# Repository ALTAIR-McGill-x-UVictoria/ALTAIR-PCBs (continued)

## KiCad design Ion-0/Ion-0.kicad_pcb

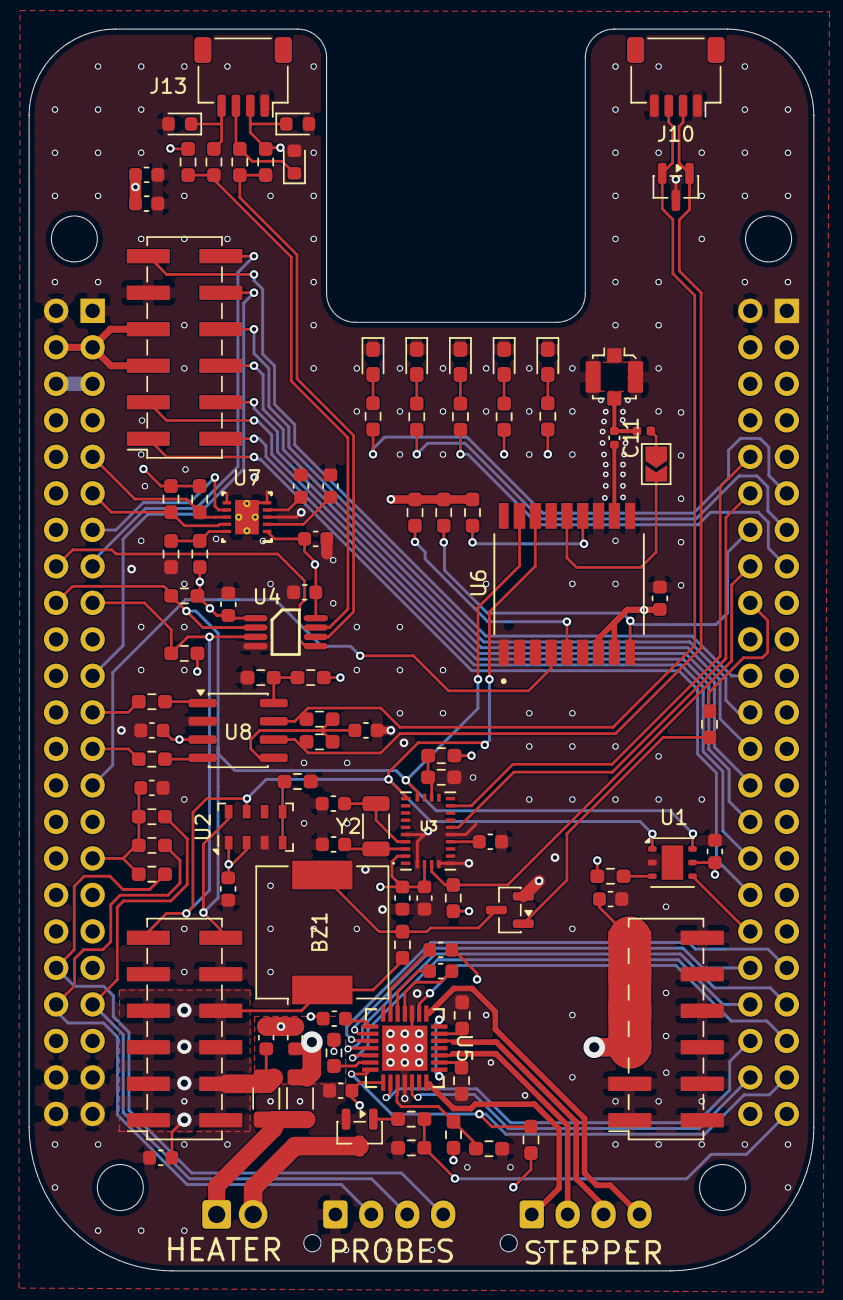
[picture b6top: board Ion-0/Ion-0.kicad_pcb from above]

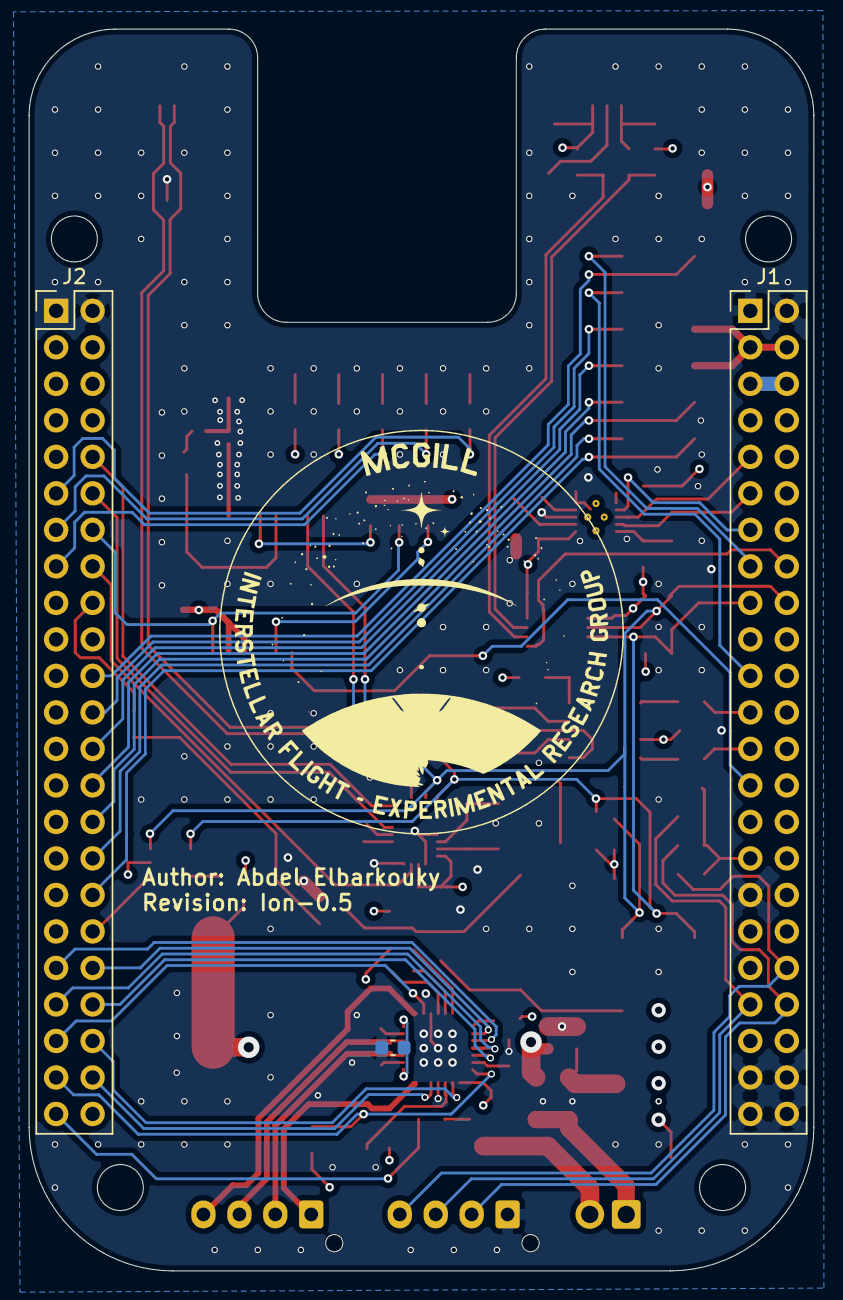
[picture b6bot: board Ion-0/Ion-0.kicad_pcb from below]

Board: 4 copper layers, 54.6 x 86.4 mm, 106 parts (3 on the bottom side), 91 nets.

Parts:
BZ1: Buzzer; Buzzer_CUI_CPT-9019S-SMT
C1, C7, C10, C12, C13, C15, C18, C19, C20, C22, C25, C26: 100nF; C_0603_1608Metric
C2, C3: 22pF; C_0603_1608Metric
C4, C5, C6: 0.1uF; C_0603_1608Metric
C8, C23: 1uF; C_0603_1608Metric
C9: 100pF; C_0603_1608Metric
C11: 47pF; C_0402_1005Metric
C14, C16, C17: 22uF; C_0603_1608Metric
C21: 4.7nF; C_0603_1608Metric
C27, C28: 0.22uF; C_0603_1608Metric
C29: 100uF; C_0603_1608Metric
D1: ESD3V3T2BHE3; SOT-23
D2, D3, D4, D5, D6: LED; LED_0603_1608Metric_Pad1.05x0.95mm_HandSolder
D7, D8, D9: TVS_3V3; D_0603_1608Metric
J1: Beaglebone-green-P9; PinHeader_2x23_P2.54mm_Vertical
J2: Beaglebone-green-P8; PinHeader_2x23_P2.54mm_Vertical
J3, J4, J5: Conn_02x06_Odd_Even; PinSocket_2x06_P2.54mm_Vertical_SMD
J6: Coaxial_Small; U.FL_Molex_MCRF_73412-0110_Vertical
J7: Conn_Probs; JST_XH_B4B-XH-AM_1x04_P2.50mm_Vertical
J8: Conn_Heater; TerminalBlock_Xinya_XY308-2.54-2P_1x02_P2.54mm_Horizontal
J10: Conn_CAN; JST_SH_SM04B-SRSS-TB_1x04-1MP_P1.00mm_Horizontal
J13: Conn_01x04; JST_SH_SM04B-SRSS-TB_1x04-1MP_P1.00mm_Horizontal
J15: Conn_01x04; JST_XH_B4B-XH-AM_1x04_P2.50mm_Vertical
JP5: SolderJumper_2_Open; SolderJumper-2_P1.3mm_Open_TrianglePad1.0x1.5mm
L1: 101nH; L_0402_1005Metric
Q1, Q2: IRLML6244; SOT-23
R4, R5, R41: 100K; R_0603_1608Metric_Pad0.98x0.95mm_HandSolder
R6, R7, R18: 4.7K; R_0603_1608Metric_Pad0.98x0.95mm_HandSolder
R8, R11, R14, R15, R16, R17, R22, R35, R36: 10K; R_0603_1608Metric_Pad0.98x0.95mm_HandSolder
R9, R25: DNI; R_0603_1608Metric_Pad0.98x0.95mm_HandSolder
R10, R24, R42, R47: 0; R_0603_1608Metric_Pad0.98x0.95mm_HandSolder
R12: 523; R_0603_1608Metric_Pad0.98x0.95mm_HandSolder
R13: 80.6; R_0603_1608Metric_Pad0.98x0.95mm_HandSolder
R19: 5K; R_0603_1608Metric_Pad0.98x0.95mm_HandSolder
R20: 20K; R_0603_1608Metric_Pad0.98x0.95mm_HandSolder
R21: 33K; R_0603_1608Metric_Pad0.98x0.95mm_HandSolder
R23, R28: 60; R_0603_1608Metric_Pad0.98x0.95mm_HandSolder
R26, R27: 33; R_0603_1608Metric_Pad0.98x0.95mm_HandSolder
R29: 100; R_0603_1608Metric_Pad0.98x0.95mm_HandSolder
R30: 470; R_0603_1608Metric_Pad0.98x0.95mm_HandSolder
R31: 1k; R_0603_1608Metric_Pad0.98x0.95mm_HandSolder
R32, R33, R34, R37, R38, R45, R46: 330; R_0603_1608Metric_Pad0.98x0.95mm_HandSolder
R39, R40: 0; R_1206_3216Metric
R43, R44: 0.05; R_0603_1608Metric_Pad0.98x0.95mm_HandSolder
U1: HDC2080; Texas_S-PWSON-N6-HDC2080
U2: MS5607-02BA; LGA-8_3x5mm_P1.25mm
U3: BNO085; IC_BNO085
U4: TCA9617ADGKR; TCA9617A
U5: A4988SETTR-T; QFN-28_ALM
U6: MAX-M10M-00B; XCVR_MAX-M10M-00B
U7: TPS3850H50DRCR; TPS3850
U8: SN65HVD230; SOIC-8_3.9x4.9mm_P1.27mm
Y2: 9HT10-32.768KBZF-T; L_1206_3216Metric

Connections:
+1V8: C23.2, J1.31, R4.1, R5.1, R41.1
+3V3: C1.1, C4.1, C5.1, C7.1, C10.2, C12.2, C15.1, C16.1, C19.2, C20.1, C22.2, C27.1, C28.1, D8.1 (A1), J1.3, J1.4, J5.5, J5.7, J13.2, R6.2, R7.1, R8.1, R9.1, R12.1, R14.1, R15.1, R16.2, R17.1, R18.2, R19.2, R21.1, R25.1, R30.1, R35.1, R36.1, R47.1, U1.5 (VDD), U2.1 (VDD), U2.2 (PS), U3.3 (VDD), U3.28 (VDDIO), U4.1 (VCCA), U4.8 (VCCB), U5.15 (VDD), U6.7 (V_IO), U6.8 (VCC), U7.1 (VDD), U8.3 (VCC)
+5V: BZ1.1 (+), C17.1, C18.1, J1.5, J1.6, J4.1, J4.2, J4.3, J4.4, J4.5, J4.6, J4.7, J4.8, R31.1, R39.1, R45.1
+12V: C13.1, C14.1, C26.1, C29.1, J3.5, J3.7, J3.9, J3.11, R40.1, U5.22 (VBB1), U5.28 (VBB2)
/AIN0: J1.40, J7.2, R5.2
/AIN1: J1.39, J7.3, R4.2
/AIN2: J1.38, J7.4, R41.2
/Buzzer: J2.18, R46.1
/CAN_RXD: J1.25, R27.1
/CAN_TXD: J1.23, R26.1
/GPS-PPS: J1.27, U6.4 (TIMEPULSE)
/Humidity-INT: J2.36, U1.4 (DRDY)
/I2C1B-EN: J1.16, U4.5 (EN)
/I2C1_SCL: J1.18, J4.12, R7.2, U1.6 (SCL), U2.8 (SCLK), U3.19 (H_SCL/SCK/RX), U4.2 (SCLA), U6.17 (SCL)
/I2C1_SDA: J1.17, J4.11, R6.1, U1.1 (SDA), U2.7 (SDI/SDA), U3.20 (H_SDA/H_MISO/TX), U4.3 (SDAA), U6.16 (SDA)
/IND-1: J2.13, R33.1
/IND-2: J2.11, R34.1
/IND_3: J2.22, J5.11
/LED_PWM_1: J1.21, J5.10
/LED_PWM_2: J1.15, J5.12
/MOTOR_1_A: J2.28, J5.4
/MOTOR_1_B: J2.32, J5.2
/MOTOR_2_A: J2.24, J5.8
/MOTOR_2_B: J2.26, J5.6
/PWM-Heaters: J2.45, R11.1, R29.1
/SERVO_1: J2.30, J5.3
/SERVO_2: J2.34, J5.1
/STATE-LED: J2.15, R32.1
/STP-DIR: J2.44, U5.19 (DIR)
/STP-MS1: J2.38, U5.9 (MS1)
/STP-MS2: J2.37, U5.10 (MS2)
/STP-MS3: J2.39, U5.11 (MS3)
/STP-STEP: J2.42, U5.16 (STEP)
/Sensor-bus-hat/CAN_N: D1.1 (A1), J10.2, R23.2, U8.6 (CANL)
/Sensor-bus-hat/CAN_P: D1.2 (A2), J10.3, R28.1, U8.7 (CANH)
/Sensor-bus-hat/CAN_Vref: C21.1, R23.1, R28.2, U8.5 (Vref)
/Sensor-bus-hat/OUT1A: J15.2, U5.24 (OUT1A)
/Sensor-bus-hat/OUT1B: J15.1, U5.21 (OUT1B)
/Sensor-bus-hat/OUT2A: J15.3, U5.26 (OUT2A)
/Sensor-bus-hat/OUT2B: J15.4, U5.1 (OUT2B)
/Sensor-bus-hat/VCC_RF: JP5.2 (B), U6.14 (VCC_RF)
/WD-INT: J1.13, U7.7 (WDI)
/~BNO-BOOT: J2.16, R8.2, U3.4 (~BOOT)
/~BNO-INT: J2.10, U3.14 (~H_INT)
/~BNO-RST: J2.12, U3.11 (~RST)
/~GPS-RST: J2.14, R17.2, U6.9 (~RESET)
/~STP-EN: J2.41, U5.2 (*ENABLE)
/~STP-RST: J2.40, U5.12 (*RESET)
/~STP-SLP: J2.43, R19.1, U5.14 (*SLEEP)
/~SYS_RST: J1.9, R15.2, U7.8 (WDO_N)
/~WD-RST: J1.11, R14.2, U7.9 (RESET_N)
GND: C1.2, C2.2, C3.2, C4.2, C5.2, C6.2, C7.2, C8.1, C9.2, C10.1, C12.1, C13.2, C14.2, C15.2, C16.2, C17.2, C18.2, C19.1, C20.2, C21.2, C22.1, C23.1, C27.2, C29.2, D1.3 (common), D2.1 (K), D3.1 (K), D4.1 (K), D5.1 (K), D6.1 (K), D7.2 (A2), D8.2 (A2), D9.2 (A2), J1.1, J1.2, J1.33, J1.43, J1.44, J1.45, J1.46, J2.1, J2.2, J3.1, J3.2, J3.3, J3.4, J3.6, J3.8, J3.10, J3.12, J4.9, J4.10, J5.9, J6.2 (Ext), J7.1, J10.1, J10.4, J13.1, Q1.2 (S), Q2.2 (S), R10.2, R11.2, R13.1, R20.1, R22.2, R24.2, R42.2, R43.2, R44.2, U1.2 (GND), U2.3 (GND), U3.2 (GND), U3.5 (PS1), U3.6 (PS0/WAKE), U3.10 (CLKSEL0), U3.25 (GNDIO), U4.4 (GND), U5.3 (GND), U5.18 (GND), U5.29, U6.1 (GND), U6.10 (GND__1), U6.12 (GND__2), U7.3 (SET0), U7.5 (GND), U7.6 (SET1), U7.11 (PAD), U8.2 (GND)
unnamed: BZ1.2 (-), Q1.3 (D), R45.2
unnamed: D2.2 (A), R30.2
unnamed: D3.2 (A), R31.2
unnamed: D4.2 (A), R32.2
unnamed: D5.2 (A), R33.2
unnamed: D6.2 (A), R34.2
unnamed: D7.1 (A1), J13.3, R38.2
unnamed: D9.1 (A1), J13.4, R37.2
unnamed: C11.1, J6.1 (In), L1.2
unnamed: J8.1, R39.2, R40.2
unnamed: J8.2, Q2.3 (D)
unnamed: JP5.1 (A), L1.1
unnamed: Q1.1 (G), R46.2
unnamed: Q2.1 (G), R29.2
unnamed: R42.1, U2.4 (CSB), U2.5 (CSB)
unnamed: R47.2, U1.3 (ADDR)
unnamed: C6.1, U3.9 (CAP)
unnamed: R9.2, R10.1, U3.17 (SA0/H_MOSI)
unnamed: C2.1, U3.27 (XIN32), Y2.1
unnamed: C3.1, U3.26 (XOUT32/CLKSEL1), Y2.2
unnamed: R36.2, R37.1, U4.7 (SCLB)
unnamed: R35.2, R38.1, U4.6 (SDAB)
unnamed: C25.1, U5.4 (CP1)
unnamed: C25.2, U5.5 (CP2)
unnamed: R21.2, R22.1, U5.17 (REF)
unnamed: R20.2, U5.13 (ROSC)
unnamed: R44.1, U5.23 (SENSE1)
unnamed: R43.1, U5.27 (SENSE2)
unnamed: C26.2, U5.6 (VCP)
unnamed: C28.2, U5.8 (VREG)
unnamed: R18.1, U6.5 (EXTINT)
unnamed: R16.1, U6.13 (LNA_EN)
unnamed: C11.2, U6.11 (RF_IN)
unnamed: C8.2, U7.4 (CRST)
unnamed: C9.1, U7.2 (CWD)
unnamed: R12.2, R13.2, U7.10 (SENSE)
unnamed: R26.2, U8.1 (D)
unnamed: R27.2, U8.4 (R)
unnamed: R24.1, R25.2, U8.8 (Rs)

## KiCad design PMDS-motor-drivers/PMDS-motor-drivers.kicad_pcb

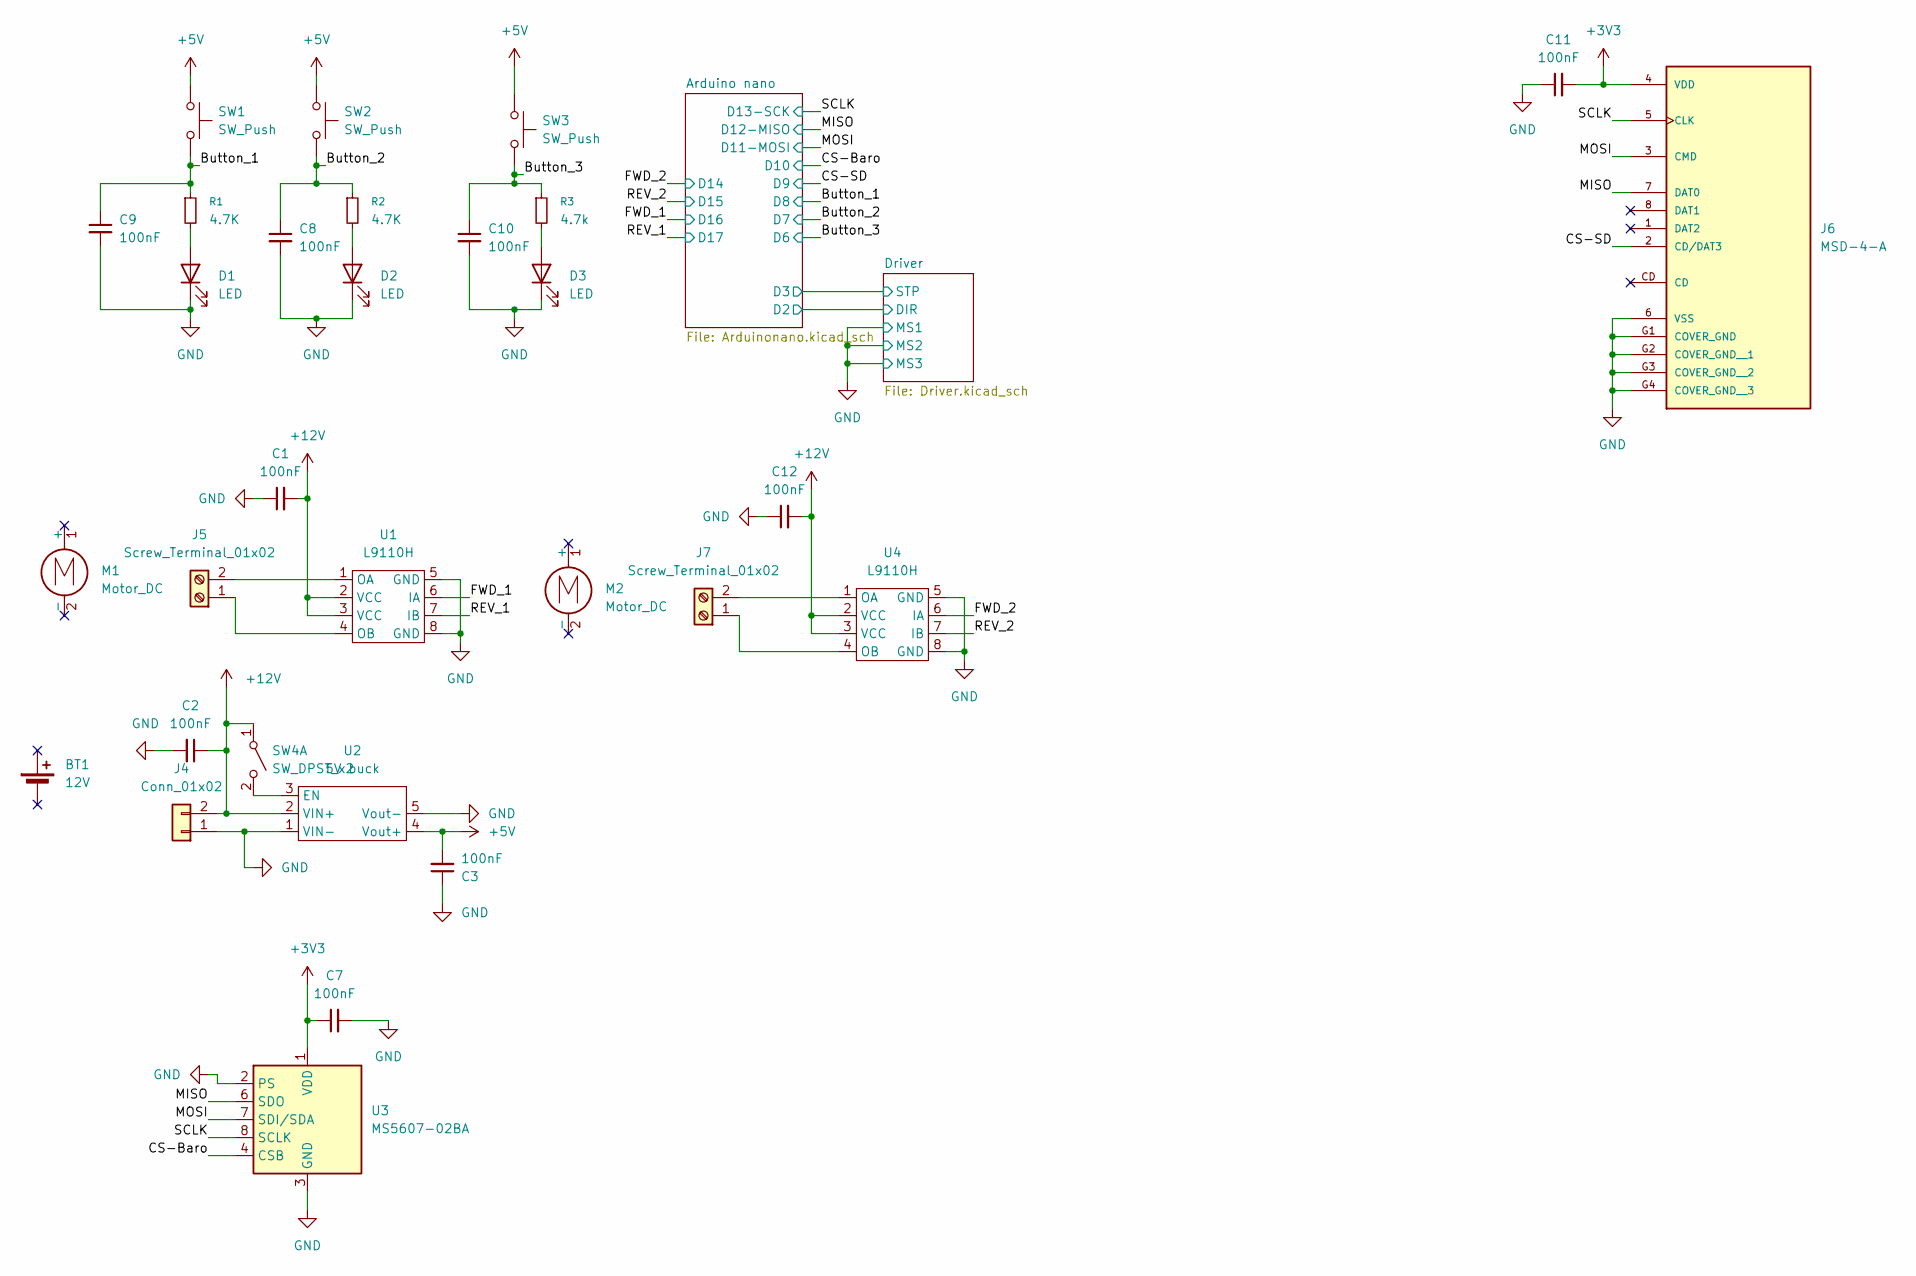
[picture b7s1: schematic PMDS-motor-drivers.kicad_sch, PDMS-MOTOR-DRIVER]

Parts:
BT1: 12V
C1, C2, C3, C7, C8, C9, C10, C11, C12: 100nF; C_0603_1608Metric
D1, D2, D3: LED; LED_0603_1608Metric
J4: Conn_01x02; AMASS_XT60IPW-M_1x03_P7.20mm_Horizontal
J5, J7: Screw_Terminal_01x02; TerminalBlock_Xinya_XY308-2.54-2P_1x02_P2.54mm_Horizontal
J6: MSD-4-A; CUI_MSD-4-A; PARTREV 1.0
M1, M2: Motor_DC
R1, R2: 4.7K; R_0603_1608Metric_Pad0.98x0.95mm_HandSolder
R3: 4.7k; R_0603_1608Metric_Pad0.98x0.95mm_HandSolder
SW1, SW2, SW3: SW_Push; SW_PUSH_6mm
SW4: SW_DPST_x2; SW_DIP_SPSTx01_Piano_10.8x4.1mm_W7.62mm_P2.54mm
U1, U4: L9110H; DIP-8_W8.89mm_SMDSocket_LongPads
U2: 5V buck; 5V-buck_psm-302-abra
U3: MS5607-02BA; LGA-8_3x5mm_P1.25mm

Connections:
+3V3: C7.1, C11.2, J6.4 (VDD), U3.1 (VDD); also elsewhere on the board
+5V: C3.2, SW1.1, SW2.1, SW3.1, U2.4 (Vout+); also elsewhere on the board
+12V: C1.2, C2.1, C12.2, J4.2, SW4.1 (A), U1.2 (VCC), U1.3 (VCC), U2.2 (VIN+), U4.2 (VCC), U4.3 (VCC); also elsewhere on the board
/Button_1: C9.1, R1.1, SW1.2; also elsewhere on the board
/Button_2: C8.1, R2.1, SW2.2; also elsewhere on the board
/Button_3: C10.1, R3.1, SW3.2; also elsewhere on the board
/CS-Baro: U3.4 (CSB), U3.5 (CSB); also elsewhere on the board
/CS-SD: J6.2 (CD/DAT3); also elsewhere on the board
/FWD_1: U1.6 (IA); also elsewhere on the board
/FWD_2: U4.6 (IA); also elsewhere on the board
/MISO: J6.7 (DAT0), U3.6 (SDO); also elsewhere on the board
/MOSI: J6.3 (CMD), U3.7 (SDI/SDA); also elsewhere on the board
/REV_1: U1.7 (IB); also elsewhere on the board
/REV_2: U4.7 (IB); also elsewhere on the board
/SCLK: J6.5 (CLK), U3.8 (SCLK); also elsewhere on the board
GND: C1.1, C2.2, C3.1, C7.2, C8.2, C9.2, C10.2, C11.1, C12.1, D1.1 (K), D2.1 (K), D3.1 (K), J4.1, J6.6 (VSS), J6.G1 (COVER_GND), J6.G2 (COVER_GND__1), J6.G3 (COVER_GND__2), J6.G4 (COVER_GND__3), U1.5 (GND), U1.8 (GND), U2.1 (VIN-), U2.5 (Vout-), U3.2 (PS), U3.3 (GND), U4.5 (GND), U4.8 (GND); also elsewhere on the board
unnamed: D1.2 (A), R1.2
unnamed: D2.2 (A), R2.2
unnamed: D3.2 (A), R3.2
unnamed: J5.1, U1.4 (OB)
unnamed: J5.2, U1.1 (OA)
unnamed: J7.1, U4.4 (OB)
unnamed: J7.2, U4.1 (OA)
unnamed: SW4.2 (B), U2.3 (EN)

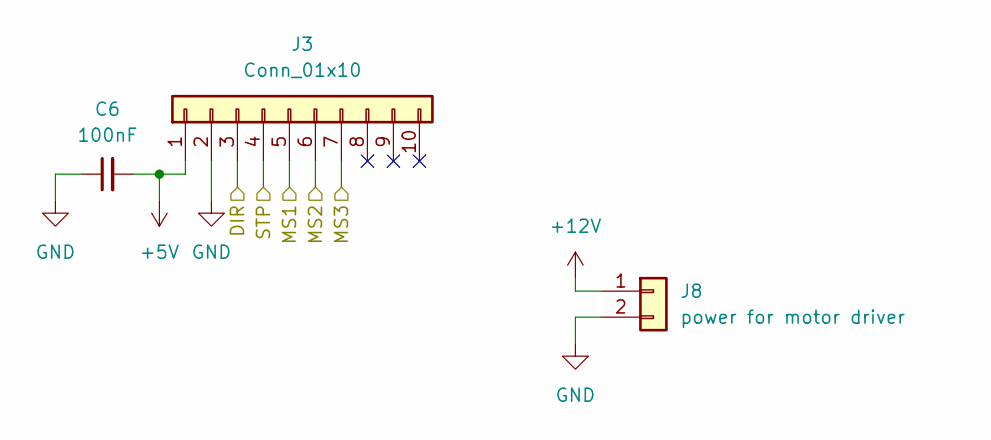
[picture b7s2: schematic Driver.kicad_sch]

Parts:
C6: 100nF; C_0603_1608Metric
J3: Conn_01x10; PinHeader_1x10_P2.54mm_Vertical
J8: power for motor driver; TerminalBlock_Xinya_XY308-2.54-2P_1x02_P2.54mm_Horizontal

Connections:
+5V: C6.2, J3.1; also elsewhere on the board
+12V: J8.1; also elsewhere on the board
/Arduino nano/D2: J3.3; also elsewhere on the board
/Arduino nano/D3: J3.4; also elsewhere on the board
GND: C6.1, J3.2, J3.5, J3.6, J3.7, J8.2; also elsewhere on the board

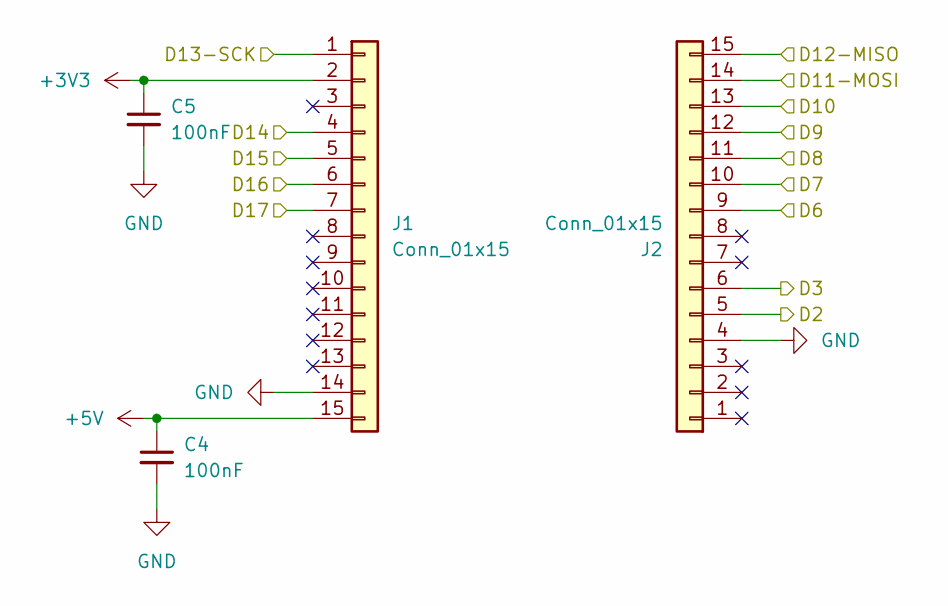
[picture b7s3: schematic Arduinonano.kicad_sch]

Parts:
C4, C5: 100nF; C_0603_1608Metric
J1, J2: Conn_01x15; PinHeader_1x15_P2.54mm_Vertical

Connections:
+3V3: C5.1, J1.2; also elsewhere on the board
+5V: C4.1, J1.15; also elsewhere on the board
/Arduino nano/D2: J2.5; also elsewhere on the board
/Arduino nano/D3: J2.6; also elsewhere on the board
/Button_1: J2.11; also elsewhere on the board
/Button_2: J2.10; also elsewhere on the board
/Button_3: J2.9; also elsewhere on the board
/CS-Baro: J2.13; also elsewhere on the board
/CS-SD: J2.12; also elsewhere on the board
/FWD_1: J1.6; also elsewhere on the board
/FWD_2: J1.4; also elsewhere on the board
/MISO: J2.15; also elsewhere on the board
/MOSI: J2.14; also elsewhere on the board
/REV_1: J1.7; also elsewhere on the board
/REV_2: J1.5; also elsewhere on the board
/SCLK: J1.1; also elsewhere on the board
GND: C4.2, C5.2, J1.14, J2.4; also elsewhere on the board

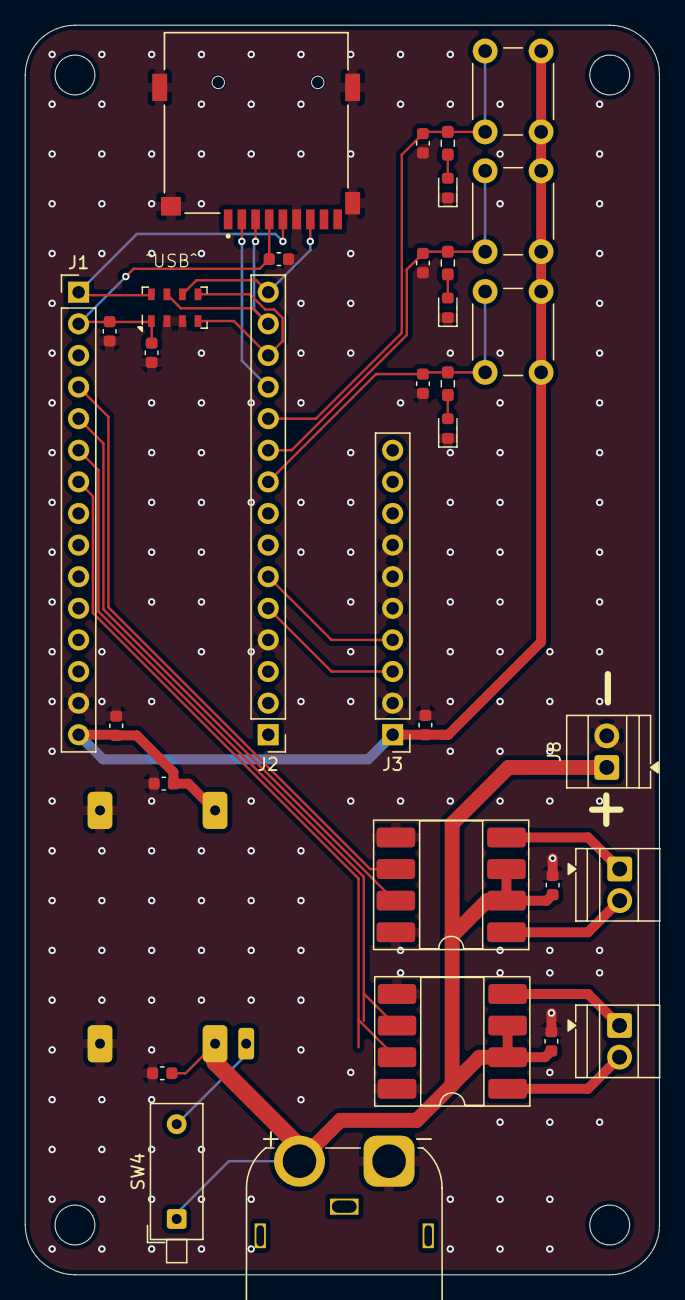
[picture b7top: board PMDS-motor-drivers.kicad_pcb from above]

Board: 2 copper layers, 51.0 x 100.4 mm, 34 parts (1 on the bottom side), 26 nets.

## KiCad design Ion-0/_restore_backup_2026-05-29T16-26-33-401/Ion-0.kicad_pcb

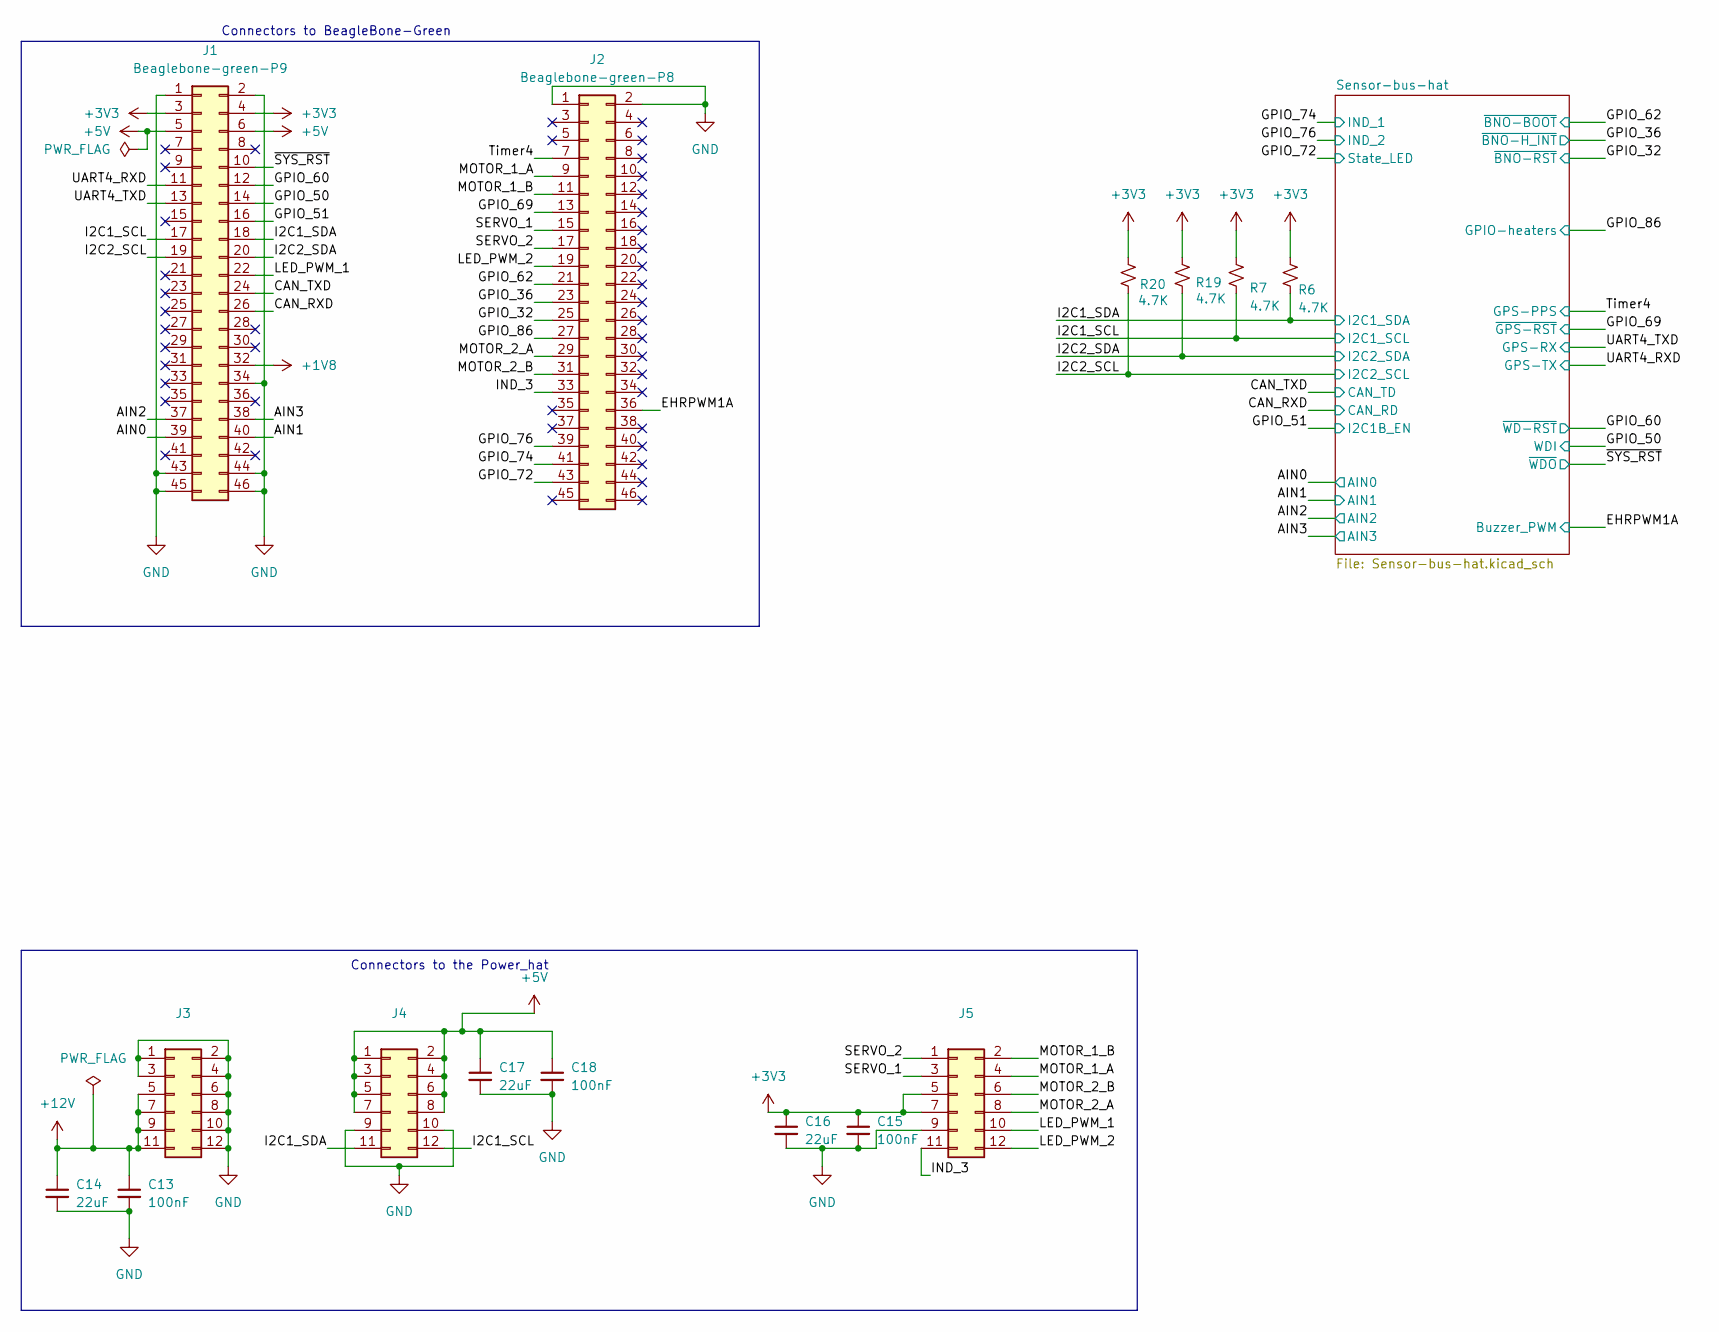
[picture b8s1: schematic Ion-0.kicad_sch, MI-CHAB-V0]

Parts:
C13, C15, C18: 100nF; C_0603_1608Metric
C14, C16, C17: 22uF; C_0603_1608Metric
J1: Beaglebone-green-P9; PinHeader_2x23_P2.54mm_Vertical
J2: Beaglebone-green-P8; PinHeader_2x23_P2.54mm_Vertical
J3, J4, J5: Conn_02x06_Odd_Even; PinSocket_2x06_P2.54mm_Vertical
R6, R7, R19, R20: 4.7K; R_0603_1608Metric_Pad0.98x0.95mm_HandSolder

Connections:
+1V8: J1.32; also elsewhere on the board
+3V3: C15.1, C16.1, J1.3, J1.4, J5.5, J5.7, R6.2, R7.1, R19.1, R20.1; also elsewhere on the board
+5V: C17.1, C18.1, J1.5, J1.6, J4.1, J4.2, J4.3, J4.4, J4.5, J4.6, J4.7, J4.8; also elsewhere on the board
+12V: C13.1, C14.1, J3.5, J3.7, J3.9, J3.11
/AIN0: J1.39; also elsewhere on the board
/AIN1: J1.40; also elsewhere on the board
/AIN2: J1.37; also elsewhere on the board
/AIN3: J1.38; also elsewhere on the board
/CAN_RXD: J1.26; also elsewhere on the board
/CAN_TXD: J1.24; also elsewhere on the board
/EHRPWM1A: J2.36; also elsewhere on the board
/GPIO_32: J2.25; also elsewhere on the board
/GPIO_36: J2.23; also elsewhere on the board
/GPIO_50: J1.14; also elsewhere on the board
/GPIO_51: J1.16; also elsewhere on the board
/GPIO_60: J1.12; also elsewhere on the board
/GPIO_62: J2.21; also elsewhere on the board
/GPIO_69: J2.13; also elsewhere on the board
/GPIO_72: J2.43; also elsewhere on the board
/GPIO_74: J2.41; also elsewhere on the board
/GPIO_76: J2.39; also elsewhere on the board
/GPIO_86: J2.27; also elsewhere on the board
/I2C1_SCL: J1.17, J4.12, R7.2; also elsewhere on the board
/I2C1_SDA: J1.18, J4.11, R6.1; also elsewhere on the board
/I2C2_SCL: J1.19, R20.2; also elsewhere on the board
/I2C2_SDA: J1.20, R19.2; also elsewhere on the board
/IND_3: J2.33, J5.11
/LED_PWM_1: J1.22, J5.10
/LED_PWM_2: J2.19, J5.12
/MOTOR_1_A: J2.9, J5.4
/MOTOR_1_B: J2.11, J5.2
/MOTOR_2_A: J2.29, J5.8
/MOTOR_2_B: J2.31, J5.6
/SERVO_1: J2.15, J5.3
/SERVO_2: J2.17, J5.1
/Timer4: J2.7; also elsewhere on the board
/UART4_RXD: J1.11; also elsewhere on the board
/UART4_TXD: J1.13; also elsewhere on the board
/~SYS_RST: J1.10; also elsewhere on the board
GND: C13.2, C14.2, C15.2, C16.2, C17.2, C18.2, J1.1, J1.2, J1.34, J1.43, J1.44, J1.45, J1.46, J2.1, J2.2, J3.1, J3.2, J3.3, J3.4, J3.6, J3.8, J3.10, J3.12, J4.9, J4.10, J5.9; also elsewhere on the board

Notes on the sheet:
Connectors to BeagleBone-Green
Connectors to the Power_hat

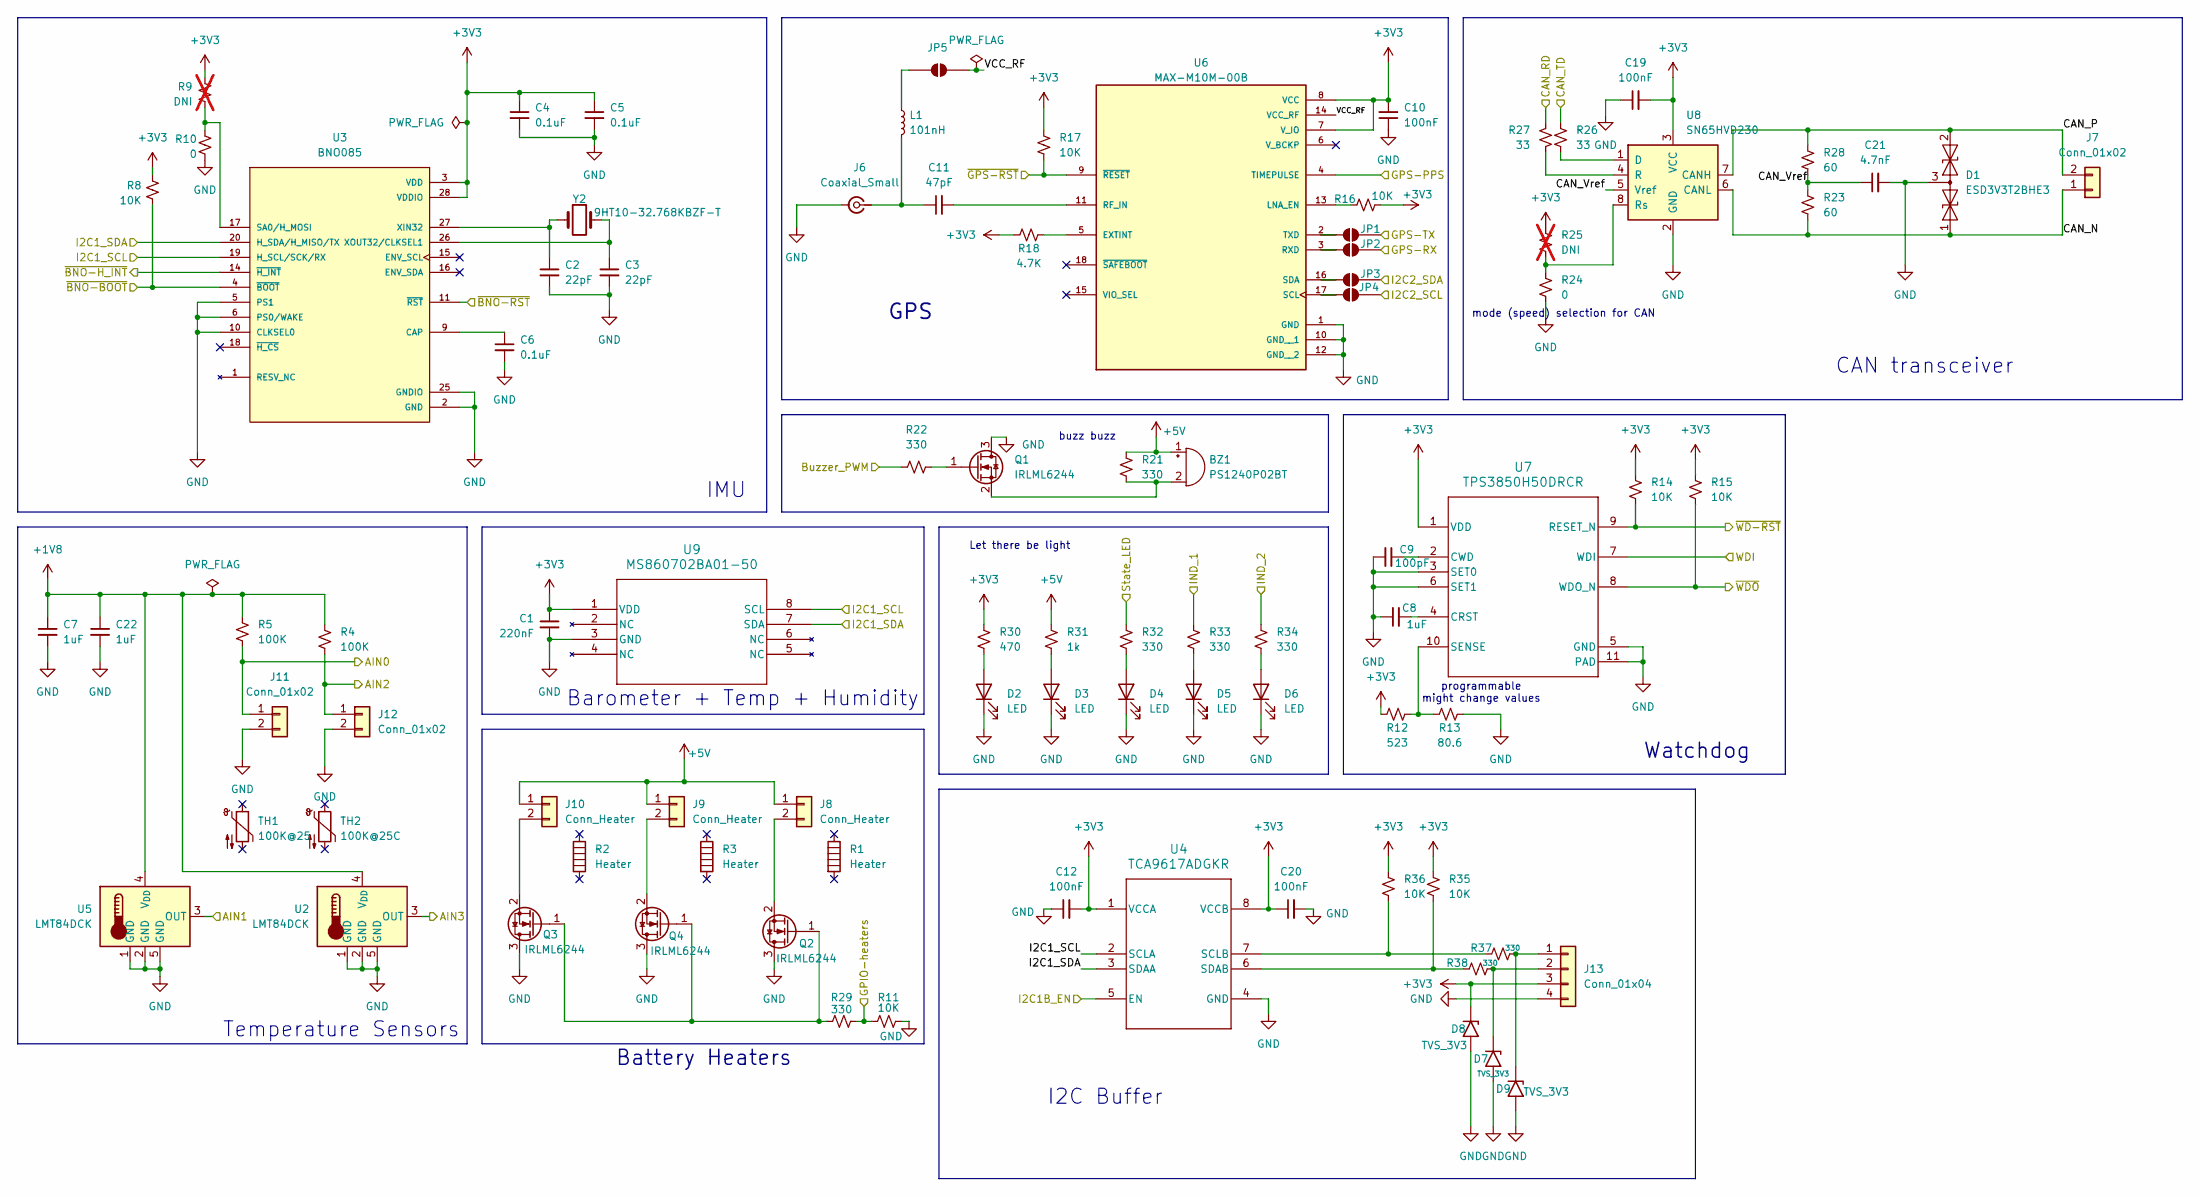
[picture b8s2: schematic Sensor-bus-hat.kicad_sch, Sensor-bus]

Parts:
BZ1: PS1240P02BT; Buzzer_TDK_PS1240P02BT_D12.2mm_H6.5mm
C1: 220nF; C_0603_1608Metric
C2, C3: 22pF; C_0603_1608Metric
C4, C5, C6: 0.1uF; C_0603_1608Metric
C7, C8, C22: 1uF; C_0603_1608Metric
C9: 100pF; C_0603_1608Metric
C10, C12, C19, C20: 100nF; C_0603_1608Metric
C11: 47pF; C_0603_1608Metric
C21: 4.7nF; C_0603_1608Metric
D1: ESD3V3T2BHE3; SOT-23
D2, D3, D4, D5, D6: LED; LED_0805_2012Metric
D7, D8, D9: TVS_3V3; D_0402_1005Metric_Pad0.77x0.64mm_HandSolder
J6: Coaxial_Small; SMA_Samtec_SMA-J-P-H-ST-EM1_EdgeMount
J7, J11, J12: Conn_01x02; JST_SH_SM02B-SRSS-TB_1x02-1MP_P1.00mm_Horizontal
J8, J9, J10: Conn_Heater; JST_SH_SM02B-SRSS-TB_1x02-1MP_P1.00mm_Horizontal
J13: Conn_01x04; JST_SH_SM04B-SRSS-TB_1x04-1MP_P1.00mm_Horizontal
JP1, JP2, JP3, JP4, JP5: SolderJumper_2_Open; SolderJumper-2_P1.3mm_Open_TrianglePad1.0x1.5mm
L1: 101nH; L_0402_1005Metric
Q1, Q2, Q3, Q4: IRLML6244; SOT-23
R1, R2, R3: Heater
R4, R5: 100K; R_0603_1608Metric_Pad0.98x0.95mm_HandSolder
R8, R11, R14, R15, R16, R17, R35, R36: 10K; R_0603_1608Metric_Pad0.98x0.95mm_HandSolder
R9, R25: DNI; R_0603_1608Metric_Pad0.98x0.95mm_HandSolder; not fitted
R10, R24: 0; R_0603_1608Metric_Pad0.98x0.95mm_HandSolder
R12: 523; R_0603_1608Metric_Pad0.98x0.95mm_HandSolder
R13: 80.6; R_0603_1608Metric_Pad0.98x0.95mm_HandSolder
R18: 4.7K; R_0603_1608Metric_Pad0.98x0.95mm_HandSolder
R21, R22, R29, R32, R33, R34, R37, R38: 330; R_0603_1608Metric_Pad0.98x0.95mm_HandSolder
R23, R28: 60; R_0603_1608Metric_Pad0.98x0.95mm_HandSolder
R26, R27: 33; R_0603_1608Metric_Pad0.98x0.95mm_HandSolder
R30: 470; R_0603_1608Metric_Pad0.98x0.95mm_HandSolder
R31: 1k; R_0603_1608Metric_Pad0.98x0.95mm_HandSolder
TH1: 100K@25
TH2: 100K@25C
U2, U5: LMT84DCK; SOT-353_SC-70-5
U3: BNO085; IC_BNO085; PARTREV v1.17
U4: TCA9617ADGKR; TCA9617A
U6: MAX-M10M-00B; XCVR_MAX-M10M-00B; PARTREV C1
U7: TPS3850H50DRCR; TPS3850
U8: SN65HVD230; SOIC-8_3.9x4.9mm_P1.27mm
U9: MS860702BA01-50; MS860702BA01-50_TEC
Y2: 9HT10-32.768KBZF-T; L_1206_3216Metric

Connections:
+1V8: C7.1, C22.1, R4.1, R5.1, U2.4 (V_{DD}), U5.4 (V_{DD}); also elsewhere on the board
+3V3: C1.1, C4.1, C5.1, C10.2, C12.2, C19.2, C20.1, D8.1 (A1), J13.3, R8.1, R9.1, R12.1, R14.1, R15.1, R16.2, R17.1, R18.2, R25.1, R30.1, R35.1, R36.1, U3.3 (VDD), U3.28 (VDDIO), U4.1 (VCCA), U4.8 (VCCB), U6.7 (V_IO), U6.8 (VCC), U7.1 (VDD), U8.3 (VCC), U9.1 (VDD); also elsewhere on the board
+5V: BZ1.1 (+), J8.1, J9.1, J10.1, R21.1, R31.1; also elsewhere on the board
/AIN0: J11.1, R5.2; also elsewhere on the board
/AIN1: U5.3 (OUT); also elsewhere on the board
/AIN2: J12.1, R4.2; also elsewhere on the board
/AIN3: U2.3 (OUT); also elsewhere on the board
/CAN_RXD: R27.1; also elsewhere on the board
/CAN_TXD: R26.1; also elsewhere on the board
/EHRPWM1A: R22.1; also elsewhere on the board
/GPIO_32: U3.11 (~RST); also elsewhere on the board
/GPIO_36: U3.14 (~H_INT); also elsewhere on the board
/GPIO_50: U7.7 (WDI); also elsewhere on the board
/GPIO_51: U4.5 (EN); also elsewhere on the board
/GPIO_60: R14.2, U7.9 (RESET_N); also elsewhere on the board
/GPIO_62: R8.2, U3.4 (~BOOT); also elsewhere on the board
/GPIO_69: R17.2, U6.9 (~RESET); also elsewhere on the board
/GPIO_72: R32.1; also elsewhere on the board
/GPIO_74: R33.1; also elsewhere on the board
/GPIO_76: R34.1; also elsewhere on the board
/GPIO_86: R11.1, R29.1; also elsewhere on the board
/I2C1_SCL: U3.19 (H_SCL/SCK/RX), U4.2 (SCLA), U9.8 (SCL); also elsewhere on the board
/I2C1_SDA: U3.20 (H_SDA/H_MISO/TX), U4.3 (SDAA), U9.7 (SDA); also elsewhere on the board
/I2C2_SCL: JP4.2 (B); also elsewhere on the board
/I2C2_SDA: JP3.2 (B); also elsewhere on the board
/Sensor-bus-hat/CAN_N: D1.1 (A1), J7.1, R23.2, U8.6 (CANL)
/Sensor-bus-hat/CAN_P: D1.2 (A2), J7.2, R28.1, U8.7 (CANH)
/Sensor-bus-hat/CAN_Vref: C21.1, R23.1, R28.2, U8.5 (Vref)
/Sensor-bus-hat/VCC_RF: JP5.2 (B), U6.14 (VCC_RF)
/Timer4: U6.4 (TIMEPULSE); also elsewhere on the board
/UART4_RXD: JP1.2 (B); also elsewhere on the board
/UART4_TXD: JP2.2 (B); also elsewhere on the board
/~SYS_RST: R15.2, U7.8 (WDO_N); also elsewhere on the board
GND: C1.2, C2.2, C3.2, C4.2, C5.2, C6.2, C7.2, C8.1, C9.2, C10.1, C12.1, C19.1, C20.2, C21.2, C22.2, D1.3 (common), D2.1 (K), D3.1 (K), D4.1 (K), D5.1 (K), D6.1 (K), D7.2 (A2), D8.2 (A2), D9.2 (A2), J6.2 (Ext), J11.2, J12.2, J13.4, Q1.3 (D), Q2.3 (D), Q3.3 (D), Q4.3 (D), R10.2, R11.2, R13.1, R24.2, U2.1 (GND), U2.2 (GND), U2.5 (GND), U3.2 (GND), U3.5 (PS1), U3.6 (PS0/WAKE), U3.10 (CLKSEL0), U3.25 (GNDIO), U4.4 (GND), U5.1 (GND), U5.2 (GND), U5.5 (GND), U6.1 (GND), U6.10 (GND__1), U6.12 (GND__2), U7.3 (SET0), U7.5 (GND), U7.6 (SET1), U7.11 (PAD), U8.2 (GND), U9.3 (GND); also elsewhere on the board
unnamed: BZ1.2 (-), Q1.2 (S), R21.2
unnamed: D2.2 (A), R30.2
unnamed: D3.2 (A), R31.2
unnamed: D4.2 (A), R32.2
unnamed: D5.2 (A), R33.2
unnamed: D6.2 (A), R34.2
unnamed: D7.1 (A1), J13.2, R38.2
unnamed: D9.1 (A1), J13.1, R37.2
unnamed: C11.1, J6.1 (In), L1.2
unnamed: J8.2, Q2.2 (S)
unnamed: J9.2, Q4.2 (S)
unnamed: J10.2, Q3.2 (S)
unnamed: JP1.1 (A), U6.2 (TXD)
unnamed: JP2.1 (A), U6.3 (RXD)
unnamed: JP3.1 (A), U6.16 (SDA)
unnamed: JP4.1 (A), U6.17 (SCL)
unnamed: JP5.1 (A), L1.1
unnamed: Q1.1 (G), R22.2
unnamed: Q2.1 (G), Q3.1 (G), Q4.1 (G), R29.2
unnamed: C6.1, U3.9 (CAP)
unnamed: R9.2, R10.1, U3.17 (SA0/H_MOSI)
unnamed: C2.1, U3.27 (XIN32), Y2.1
unnamed: C3.1, U3.26 (XOUT32/CLKSEL1), Y2.2
unnamed: R36.2, R37.1, U4.7 (SCLB)
unnamed: R35.2, R38.1, U4.6 (SDAB)
unnamed: R18.1, U6.5 (EXTINT)
unnamed: R16.1, U6.13 (LNA_EN)
unnamed: C11.2, U6.11 (RF_IN)
unnamed: C8.2, U7.4 (CRST)
unnamed: C9.1, U7.2 (CWD)
unnamed: R12.2, R13.2, U7.10 (SENSE)
unnamed: R26.2, U8.1 (D)
unnamed: R27.2, U8.4 (R)
unnamed: R24.1, R25.2, U8.8 (Rs)

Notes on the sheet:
Barometer + Temp + Humidity
Watchdog
IMU
Let there be light
buzz buzz
CAN transceiver
programmable might change values
GPS
I2C Buffer
mode (speed) selection for CAN
Battery Heaters
Temperature Sensors
